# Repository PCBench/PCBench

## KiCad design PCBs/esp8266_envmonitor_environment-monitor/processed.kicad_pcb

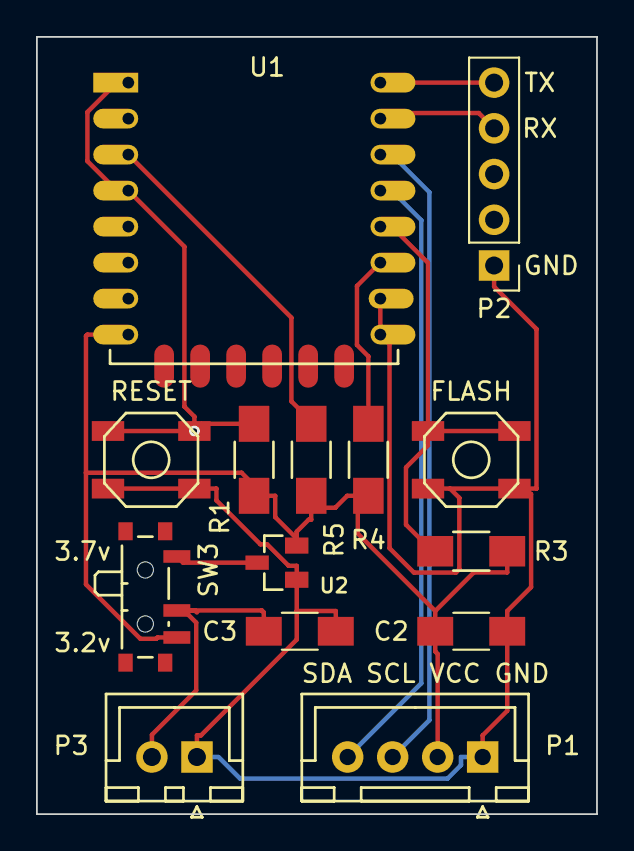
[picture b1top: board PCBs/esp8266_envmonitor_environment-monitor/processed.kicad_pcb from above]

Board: 2 copper layers, 31.1 x 43.2 mm, 14 parts (0 on the bottom side), 12 nets.

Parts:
C2: 10uF; C_1206_HandSoldering
C3: 1uF; C_1206_HandSoldering
P1: BME280; JST_XH_B04B-XH-A_04x2.50mm_Straight
P2: SERIAL; Pin_Header_Straight_1x05_Pitch2.54mm
P3: PWR; JST_XH_B02B-XH-A_02x2.50mm_Straight
R1, R3, R4, R5: 4.7k; R_1206_HandSoldering
SW1: RESET; SKQGAFE010_Switch
SW2: FLASH; SKQGAFE010_Switch
SW3: Switch_SPDT_x2; SW_SPDT_PCM12
U1: ESP-12F; ESP-12E
U2: MCP1700T; SOT-23

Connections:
/CH_EN: R5.2, U1.3
/FLASH: R3.2, SW2.1, SW2.2, U1.18
/RXD: P2.4, U1.21
/SCL: P1.3, U1.20
/SDA: P1.4, U1.19
/TXD: P2.5, U1.22
GND: C2.2, C3.2, P1.1, P2.1, P3.1, SW1.1, SW1.2, SW2.3, SW2.4, U1.15, U1.16, U2.1
unnamed: C3.1, P3.2, SW3.2
unnamed: R1.2, SW1.3, SW1.4, U1.1, U1.4
unnamed: R4.2, U1.17
unnamed: SW3.1, U2.3
VCC: C2.1, P1.2, R1.1, R3.1, R4.1, R5.1, SW3.3, U1.8, U2.2

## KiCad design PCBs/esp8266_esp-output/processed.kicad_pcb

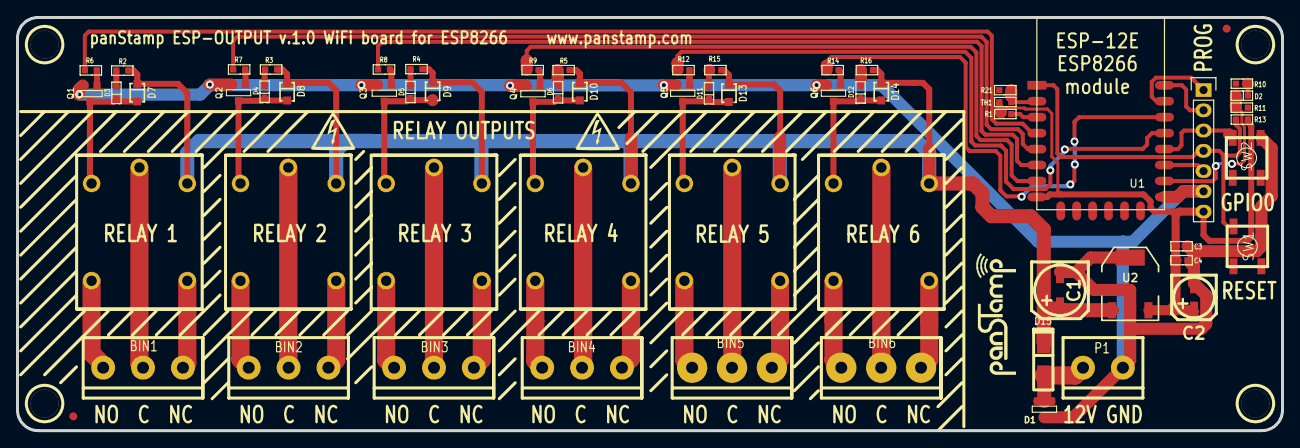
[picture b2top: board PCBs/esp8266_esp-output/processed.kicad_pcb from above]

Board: 2 copper layers, 158.6 x 51.8 mm, 67 parts (0 on the bottom side), 55 nets.

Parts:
1PIN, 1PIN_2, 1PIN_3, 1PIN_4: P***; 1pin
BIN1, BIN2, BIN3, BIN4, BIN5, BIN6: CONN_3; terminal_block_5mm_3P
C1: 47u; SMDCPOL_6.3
C2: 22u; SMDCPOL_5
C3: 1u; SM0603S
C4: 100n; SM0603S
D1: D_Schottky_x2_ACom_KKA; SOT23
D2, D3, D4, D5, D6, D11, D12: LED; SM0603S_POL
D7, D8, D9, D10, D13, D14: DIODE; SOD323
D15: D_Schottky; SMA
P1: CONN_2; terminal_block_5mm_2P
PROG0: CONN_01X07; Pin_Header_Straight_1x07
Q1, Q2, Q3, Q4, Q5, Q6: NPN; SOT23EBC
R1, R11, R13, R21: 10k; SM0603S
R2, R3, R4, R5, R15, R16: 1k5; SM0603S
R6, R7, R8, R9, R12, R14: 2k2; SM0603S
R10: 470; SM0603S
SW1, SW2: SW_PUSH_SMALL; switch-tact-noah
TH1: THERMISTOR; SM0603S
U1: ESP-12E
U2: UA78M33; SOT223
U3, U4, U5, U6, U7, U8: SONGLE_RELAY_10A
fiducial: VAL**; fiducial
fiducial_2: VAL**; fiducial

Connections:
+3.3V: C2.1, C3.1, C4.1, PROG0.7, R1.2, R13.2, TH1.1, U1.8, U2.3
+12C: C1.1, D7.1, D8.1, D9.1, D10.1, D13.1, D14.1, D15.1, R2.2, R3.1, R4.1, R5.1, R15.1, R16.1, U2.1, U3.1, U4.1, U5.1, U6.1, U7.1, U8.1
+12V: D1.1, D1.2, D15.2, P1.1
/ADC: R21.1, TH1.2, U1.2
/GPIO0: PROG0.3, SW2.2, U1.18
/GPIO2: PROG0.5, U1.17
/GPIO15: D2.2, R11.2, U1.16
/RESET: PROG0.4, R13.1, SW1.2, U1.1
/RXD: PROG0.1, U1.21
/TXD: PROG0.2, U1.22
BINOUT0: R6.1, U1.4
BINOUT1: R7.1, U1.5
BINOUT2: R8.1, U1.6
BINOUT3: R9.1, U1.7
BINOUT4: R12.1, U1.19
BINOUT5: R14.1, U1.20
GND: C1.2, C2.2, C3.2, C4.2, D1.3, P1.2, PROG0.6, Q1.1, Q2.1, Q3.1, Q4.1, Q5.1, Q6.1, SW1.1, SW2.1, U1.15, U2.2, U2.4
unnamed: BIN1.1, U3.4
unnamed: BIN1.2, U3.2
unnamed: BIN1.3, U3.5
unnamed: BIN2.1, U4.4
unnamed: BIN2.2, U4.2
unnamed: BIN2.3, U4.5
unnamed: BIN3.1, U5.4
unnamed: BIN3.2, U5.2
unnamed: BIN3.3, U5.5
unnamed: BIN4.1, U6.4
unnamed: BIN4.2, U6.2
unnamed: BIN4.3, U6.5
unnamed: BIN5.1, U7.4
unnamed: BIN5.2, U7.2
unnamed: BIN5.3, U7.5
unnamed: BIN6.1, U8.4
unnamed: BIN6.2, U8.2
unnamed: BIN6.3, U8.5
unnamed: D2.1, R10.2
unnamed: D3.1, D7.2, Q1.3, U3.3
unnamed: D3.2, R2.1
unnamed: D4.1, D8.2, Q2.3, U4.3
unnamed: D4.2, R3.2
unnamed: D5.1, D9.2, Q3.3, U5.3
unnamed: D5.2, R4.2
unnamed: D6.2, R5.2
unnamed: D6.1, D10.2, Q4.3, U6.3
unnamed: D11.1, D13.2, Q5.3, U7.3
unnamed: D11.2, R15.2
unnamed: D12.1, D14.2, Q6.3, U8.3
unnamed: D12.2, R16.2
unnamed: Q1.2, R6.2
unnamed: Q2.2, R7.2
unnamed: Q3.2, R8.2
unnamed: Q4.2, R9.2
unnamed: Q5.2, R12.2
unnamed: Q6.2, R14.2
unnamed: R1.1, U1.3

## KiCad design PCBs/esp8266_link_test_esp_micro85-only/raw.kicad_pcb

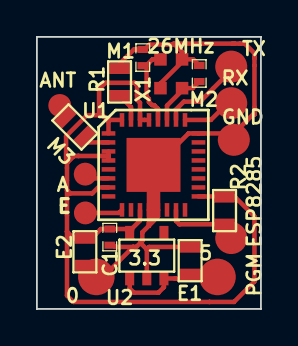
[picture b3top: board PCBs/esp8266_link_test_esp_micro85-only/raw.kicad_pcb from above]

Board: 2 copper layers, 12.4 x 15.1 mm, 20 parts (0 on the bottom side), 13 nets.

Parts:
C1: .1u; SM0402
E1, E2: 10u; SM0603
M1, M2: 5.6p; SM0402
M3: 5.6p; SM0603
P1: RX; .1SMTPIN
P2: TX; .1SMTPIN
P3: GND; .1SMTPIN
P4: ANT; .1SMTPIN
P5: A; .1SMTPIN
P6: 0; .1SMTPIN
P7: 5; .1SMTPIN
P8: PGM; .1SMTPIN
P9: E; .1SMTPIN
R1, R2: 12k; SM0603
U1: ESP8285; QFN32
U2: 3.3; SOT23-5
X1: 26MHz; XTAL4TINY

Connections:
+3.3V: C1.2, E2.2, R2.1, U1.1, U1.3, U1.4, U1.7, U1.11, U1.17, U1.29, U1.30, U1.32, U2.5
+5V: E1.2, P7.1, U2.1, U2.3
GND: C1.1, E1.1, E2.1, M1.2, M2.2, P3.1, P6.1, R1.1, U1.12, U1.13, U1.24, U1.33, U2.2, X1.3, X1.4
unnamed: P5.1, U1.6
unnamed: P2.1, U1.26
unnamed: P1.1, U1.25
unnamed: P8.1, R2.2, U1.15
unnamed: P9.1, U1.9
unnamed: M1.1, U1.28, X1.1
unnamed: M3.2, U1.2
unnamed: M2.1, U1.27, X1.2
unnamed: R1.2, U1.31
unnamed: M3.1, P4.1

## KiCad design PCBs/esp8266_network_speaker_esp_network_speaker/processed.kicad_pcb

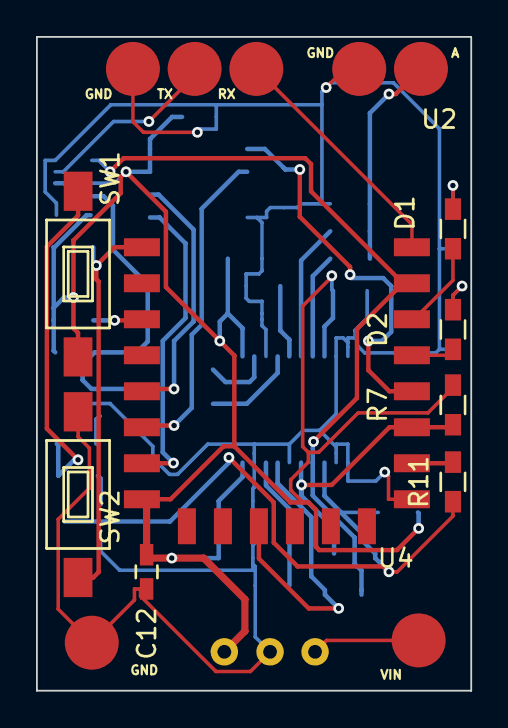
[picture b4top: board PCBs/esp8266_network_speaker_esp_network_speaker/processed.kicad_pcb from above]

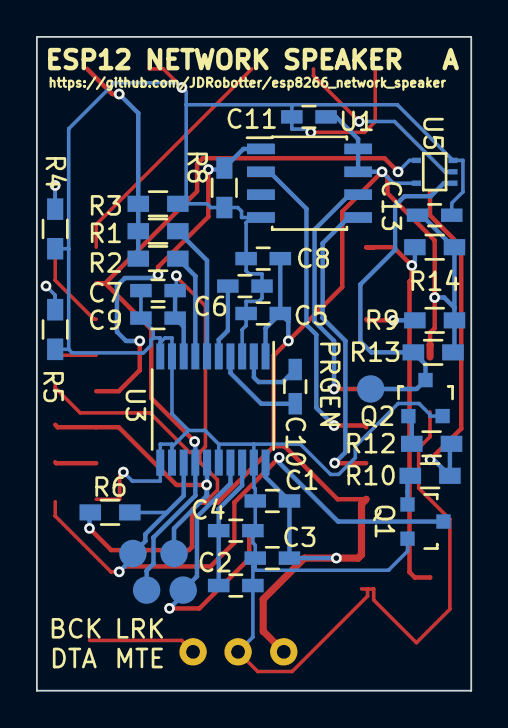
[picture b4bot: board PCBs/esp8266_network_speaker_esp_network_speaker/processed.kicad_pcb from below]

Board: 2 copper layers, 24.1 x 36.3 mm, 50 parts (34 on the bottom side), 31 nets.

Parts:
BCK: TEST_1P; Measurement_Point_Round-SMD-Pad_Small
C1, C2, C8, C9, C11, C12, C13: 100nF; C_0603_HandSoldering
C3, C4, C5, C7: 10uF; C_0603_HandSoldering
C6, C10: 2.2uF; C_0603_HandSoldering
D1, D2: LED; R_0603_HandSoldering
DTA: TEST_1P; Measurement_Point_Round-SMD-Pad_Small
LRK: TEST_1P; Measurement_Point_Round-SMD-Pad_Small
MTE: TEST_1P; Measurement_Point_Round-SMD-Pad_Small
PRGEN: TEST_1P; Measurement_Point_Round-SMD-Pad_Small
Q1, Q2: Q_NPN_BEC; SOT-23
R1, R2: 470; R_0603_HandSoldering
R3, R6, R7, R8, R9, R13, R14: 10k; R_0603_HandSoldering
R4, R5: 220; R_0603_HandSoldering
R10, R12: 1k; R_0603_HandSoldering
R11: 100; R_0603_HandSoldering
SW1, SW2: SW_PUSH; SW_SPST_FSMSM
U1: 23LC1024; SOIC-8_3.9x4.9mm_Pitch1.27mm
U2: ESP12
U3: PCM5100A; TSSOP-20_4.4x6.5mm_Pitch0.65mm
U4: TSR_1-2433; TSR-1
U5: M74VHC1GT125; SOT-353
W7: AOUT; Measurement_Point_Round-SMD-Pad_Big
W8: AGND; Measurement_Point_Round-SMD-Pad_Big
W9: PBATT; Measurement_Point_Round-SMD-Pad_Big
W10: PGND; Measurement_Point_Round-SMD-Pad_Big
W11: PROG_GND; Measurement_Point_Round-SMD-Pad_Big
W12: PROG_RX; Measurement_Point_Round-SMD-Pad_Big
W13: PROG_TX; Measurement_Point_Round-SMD-Pad_Big

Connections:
+3V3: C1.1, C3.1, C5.1, C7.1, C8.1, C9.1, C11.1, C12.1, C13.1, R6.1, R7.1, R9.2, R13.1, R14.1, SW1.1, U1.7, U1.8, U2.8, U3.1, U3.8, U3.20, U4.3, U5.5
/PROG_EN: PRGEN.1, Q2.3, R13.2, U5.1
/PROG_TX: U5.2, W13.1
/VBATT: U4.1, W9.1
DAC_BCK: BCK.1, Q1.3, R6.2, R11.1, U3.13
DAC_DATA: DTA.1, U2.21, U3.14, U5.4
DAC_LRCK: LRK.1, R7.2, U2.17, U3.15
DAC_MUTE: MTE.1, U2.11, U3.17
DAC_OUTL: R1.2, U3.6
DAC_OUTR: R2.2, U3.7
ESP12_CLK: U1.6, U2.5
ESP12_CS: R8.1, U1.1, U2.18
ESP12_MISO: U1.2, U2.6
ESP12_MOSI: U1.5, U2.7
ESP12_RESET: R14.2, SW2.1, U2.1
ESP12_TX: U2.22, W12.1
GND: C1.2, C2.1, C3.2, C4.2, C5.2, C6.1, C7.2, C8.2, C9.2, C11.2, C12.2, C13.2, Q1.2, Q2.2, R3.2, R4.1, R5.1, R8.2, SW2.2, U1.4, U2.15, U3.3, U3.9, U3.10, U3.11, U3.12, U3.16, U3.19, U4.2, U5.3, W8.1, W10.1, W11.1
LEDA: D2.2, U2.19
LEDB: D1.2, U2.20
unnamed: C2.2, C4.1, U3.18
unnamed: C6.2, U3.5
unnamed: C10.1, U3.2
unnamed: C10.2, U3.4
unnamed: D1.1, R4.2
unnamed: D2.1, R5.2
unnamed: Q1.1, R10.1
unnamed: Q2.1, R12.1
unnamed: R1.1, R2.1, R3.1, W7.1
unnamed: R9.1, U2.3
unnamed: R10.2, R12.2, SW1.2
unnamed: R11.2, U2.16

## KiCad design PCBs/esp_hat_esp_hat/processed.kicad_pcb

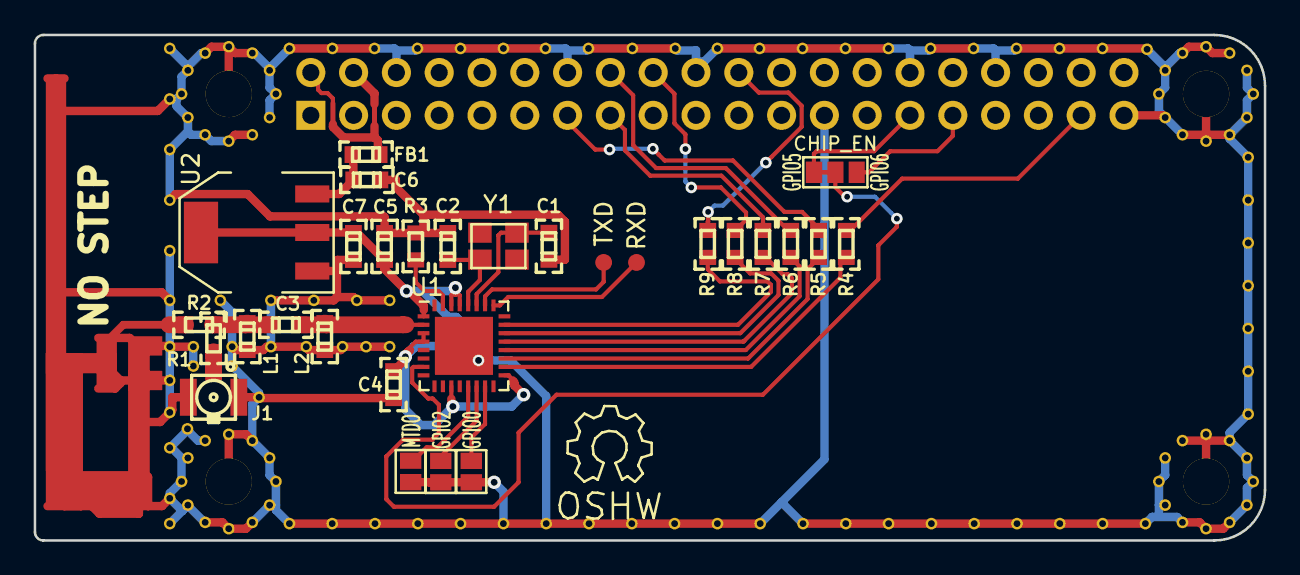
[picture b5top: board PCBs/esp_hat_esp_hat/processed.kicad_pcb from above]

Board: 2 copper layers, 73.0 x 30.0 mm, 35 parts (1 on the bottom side), 30 nets.

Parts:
ANT1: ANT_INVERTED_F; TI_DN007_2.4GHz
C1, C2: 10pF; 0603(1608m)-CHIP-CAP
C3: 5.6pF; 0603(1608m)-CHIP-CAP
C4, C5: 0.1uF; 0603(1608m)-CHIP-CAP
C6, C7: 10uF; 0603(1608m)-CHIP-CAP
FB1: FILTER; 0603(1608m)-CHIP-CAP
J1: DNP; U.FL-COAX
JP1: CHIP_EN; GS3
JP2: MTDO; GS2
JP3: GPIO2; GS2
JP4: GPIO0; GS2
L1, L2: DNP; 0603(1608m)-CHIP-CAP
P1: CONN_02X20; Socket_Strip_Straight_2x20_pi
R1: DNP; 0603(1608m)-CHIP-RESISTOR
R2: 0; 0603(1608m)-CHIP-RESISTOR
R3: 12.0K 1%; 0603(1608m)-CHIP-RESISTOR
R4, R5, R6, R7, R8, R9: 200; 0603(1608m)-CHIP-RESISTOR
U1: ESP8266EX; QFN-32-1EP_5x5mm_Pitch0.5mm
U2: AP1117D33; SOT-223-REG_VOUTSLUG
W1: RXD; Measurement_Point_Round-SMD-Pad_Small
W2: TXD; Measurement_Point_Round-SMD-Pad_Small
W3, W4, W5, W6: MOUNT; NPTH_Hole_2_75mm
Y1: 26MHz 10ppm; crystal_FA238-TSX3225

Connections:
+3V3: C4.1, C5.1, C7.1, U1.1, U1.3, U1.4, U1.11, U1.17, U1.29, U1.30, U2.2
+5V: FB1.1, P1.2, P1.4
/5V_filt: C6.1, FB1.2, U2.3
/50ohm_LNA: C3.1, L2.1, U1.2
/50ohm_ant: ANT1.2, R2.1
/50ohm_filt: C3.2, L1.1, R1.1, R2.2
/50ohm_ufl: J1.1, R1.2
GND: ANT1.1, C1.2, C2.2, C4.2, C5.2, C6.2, C7.2, J1.2, J1.3, JP2.2, JP3.2, JP4.2, L1.2, L2.2, P1.6, P1.14, P1.20, P1.25, P1.30, P1.34, P1.39, R3.1, U1.33, U2.1, W3.1, W4.1, W5.1, W6.1
GPIO5: JP1.1, JP1.2, P1.29, U1.7
GPIO6: JP1.3, P1.31
unnamed: C1.1, U1.27, Y1.1
unnamed: C2.1, U1.28, Y1.2
unnamed: JP2.1, U1.13
unnamed: JP3.1, U1.14
unnamed: JP4.1, U1.15
unnamed: R3.2, U1.31
unnamed: R4.2, U1.18
unnamed: R5.2, U1.19
unnamed: R6.2, U1.20
unnamed: R7.2, U1.21
unnamed: R8.2, U1.22
unnamed: R9.2, U1.23
unnamed: U1.25, W1.1
unnamed: U1.26, W2.1
SD_CLK: P1.15, R7.1
SD_CMD: P1.16, R6.1
SD_D0: P1.18, R8.1
SD_D1: P1.22, R9.1
SD_D2: P1.37, R4.1
SD_D3: P1.13, R5.1

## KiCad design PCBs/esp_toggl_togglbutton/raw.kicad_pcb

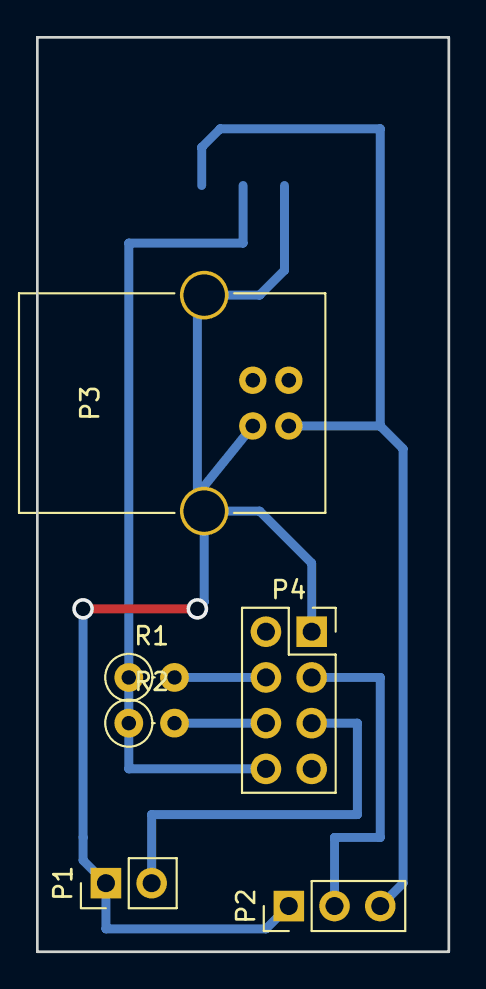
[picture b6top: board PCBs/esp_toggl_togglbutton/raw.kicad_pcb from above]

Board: 2 copper layers, 22.9 x 50.8 mm, 7 parts (1 on the bottom side), 7 nets.

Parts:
P1: Button; Pin_Header_Straight_1x02_Pitch2.54mm
P2: WS2812B; Pin_Header_Straight_1x03_Pitch2.54mm
P3: USB_B
P4: CONN_02X04; Socket_Strip_Straight_2x04_Pitch2.54mm
R1, R2: 10k; R_Axial_DIN0207_L6.3mm_D2.5mm_P2.54mm_Vertical
U1: NCP1117ST33T3G; SOT-223

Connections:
+5V: P2.3, P3.1, U1.3
GND: P1.1, P2.1, P3.4, P3.5, P4.1, U1.1
unnamed: P1.2, P4.5
unnamed: P2.2, P4.3
unnamed: P4.4, R1.2
unnamed: P4.6, R2.2
unnamed: P4.8, R1.1, R2.1, U1.2

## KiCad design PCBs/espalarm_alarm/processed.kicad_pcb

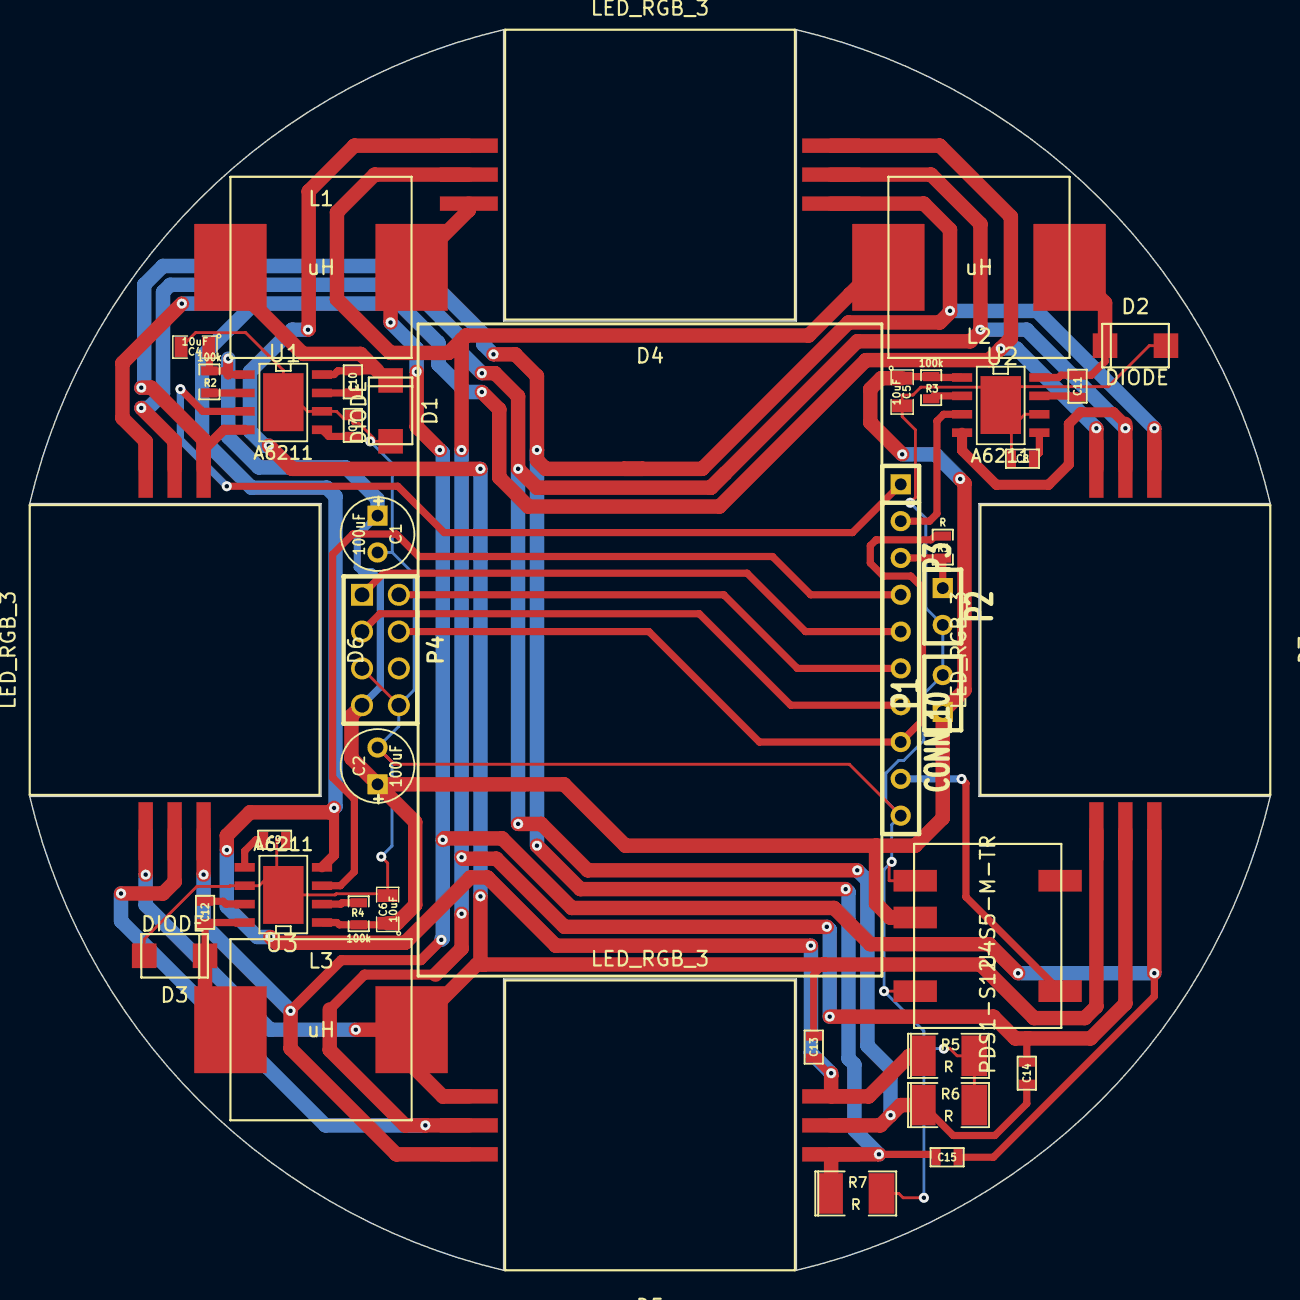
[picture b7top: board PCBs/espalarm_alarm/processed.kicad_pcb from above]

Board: 2 copper layers, 85.6 x 85.6 mm, 39 parts (0 on the bottom side), 29 nets.

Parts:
C1, C2: 100uF; C1V5
C4, C5, C6: 10uF; SM0805
C7, C8, C9, C10, C11, C12: 100nF; SM0603
C13, C14, C15: 1uF; SM0603
D1, D2, D3: DIODE; DIODE_SMA
D4, D5, D6, D7: LED_RGB_3; RGB_LED_10W
L1, L2, L3: uH; IND_12.5x12.5mm
P1, P2: CONN_2; SIL-2
P3: CONN_10; SIL-10
P4: CONN_8; pin_array_4x2
R1: R; SM0603_Resistor
R2, R3, R4: 100k; SM0603_Resistor
R5, R6, R7: R; SM1210L
U1, U2, U3: A6211; SO8_WITH_EP
U4: PDS1-S12-S5-M-TR

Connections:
/3.3V: P3.8, P4.4, R1.1
/5V: P3.9, U4.5
/12V: C1.1, C2.1, C4.1, C5.1, C6.1, P1.1, P4.7, R2.1, R3.1, R4.1, U1.1, U2.1, U3.1, U4.2
/GPIO0: P3.7, P4.3
/GPIO2: P3.6, P4.2
/GPIO12: P3.2, U2.3
/GPIO13: P3.4, U3.3
/GPIO14: P3.1, U1.3
/GPIO15: P3.5, P4.1
/GPIO16: P2.1, P3.3, R1.2
GND: C1.2, C2.2, C4.2, C5.2, C6.2, C7.2, C8.2, C9.2, D1.1, D2.1, D3.1, P1.2, P2.2, P3.10, P4.5, P4.8, R5.2, R6.2, R7.2, U1.6, U1.9, U2.6, U2.9, U3.6, U3.9, U4.1, U4.4
unnamed: C14.2, D4.5, D5.5, D6.5, D7.5, R6.1, U2.4
unnamed: C11.1, U2.7
unnamed: C11.2, D2.2, L2.1, U2.8
unnamed: R3.2, U2.2
unnamed: C9.1, U3.5
unnamed: R4.2, U3.2
unnamed: C8.1, U2.5
unnamed: C10.1, U1.7
unnamed: C10.2, D1.2, L1.1, U1.8
unnamed: C12.1, U3.7
unnamed: C12.2, D3.2, L3.1, U3.8
unnamed: C13.1, D4.1, D5.1, D6.1, D7.1, L3.2
unnamed: C7.1, U1.5
unnamed: C15.1, D4.3, D5.3, D6.3, D7.3, L1.2
unnamed: R2.2, U1.2
unnamed: C15.2, D4.4, D5.4, D6.4, D7.4, R7.1, U1.4
unnamed: C13.2, D4.6, D5.6, D6.6, D7.6, R5.1, U3.4
unnamed: C14.1, D4.2, D5.2, D6.2, D7.2, L2.2

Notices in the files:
PCBs/esp8266_envmonitor_environment-monitor/processed.kicad_pcb:
Solderpad Hardware License version 0.51
